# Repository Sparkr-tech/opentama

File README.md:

# OpenTama - An open-source reference design for MCUGotchi

## Synopsis

OpenTama is an open-source development board serving educational purposes, specifically designed for [MCUGotchi](https://github.com/jcrona/mcugotchi/) using [KiCad](https://www.kicad.org/).

It features:
* a low-power STM32L072CBT MCU
* either a backlit 128x64 LCD UC1701x or a 128x64 OLED SSD1306 display
* an RGB LED for notifications
* a piezoelectric speaker
* a 1000mAh battery
* a USB C connector for data and charging
* three buttons

Being an open-source hardware design, anyone can manufacture his/her own board. Furthermore, all components have been placed on the top side of the board, so that the assembly as well can be performed by EMS such as JLCPCB, even for small quantities. The battery and screen must be soldered manually.

## Build instructions
### Hardware

1. Make or buy an OpenTama board

	If you decide to build it, please note that the JLCPCB references for all the components have already been provided in the project. However, those have been selected depending on their availability at a specific point in time, and will probably need adjustments if you decide to go with JLCPCB.

2. Decide if you want an SSD1306 OLED screen or a UC1701x LCD screen, and buy it

	The UC1701x LCD is a low power display compared to the SSD1306 OLED that drains way more power. However, if you plan to use the MCUGotchi firmware, the highest power consumption will come from the MCU that will not really have time to sleep, so your choice will not have a big impact on the overall power consumption.

	If you want to use an SSD1306, the board expects a regular 7-pin 0,96" integrated module. However, if you want a UC1701x, you just need the LCD itself, and you can either choose an FPC one (0.5mm pitch, 14 pins), or one that needs to be soldered (0.6mm pitch, 14 pins).  
For reference, we used [this one](https://www.aliexpress.com/item/32828607106.html).

3. Buy a a battery

	The design has been made assuming a 1000mAh 40x30x12mm Li-Po/Li-ion battery.  
For reference, we used [this one](https://www.aliexpress.com/item/4000742443431.html).

4. Plug or solder the display

5. Solder the battery

6. Your OpenTama board is ready !

### Software
1. Build the firmware of your choosing

	For instance, checkout the [MCUGotchi](https://github.com/jcrona/mcugotchi/) repository and follow the instructions to build it for the OpenTama board.

2. Get and build [dfu-util](http://dfu-util.sourceforge.net/)

3. Boot the board in DFU mode

	Close the BOOT0 jumper at the top of the board, and while doing so, trigger a reset by connecting together the NRST and GND pins at the right of the board.

4. Program the board using __dfu-util__
```
$ cd mcugotchi
$ sudo make flash
```
or
```
$ sudo dfu-util -a 0 -s 0x08000000:leave -D <firmware.bin>
```

5. Enjoy !

## License

OpenTama is distributed under the CERN-OHL-S v2 license. See the LICENSE file for more information.

__  
Copyright (C) 2022 Sparkr

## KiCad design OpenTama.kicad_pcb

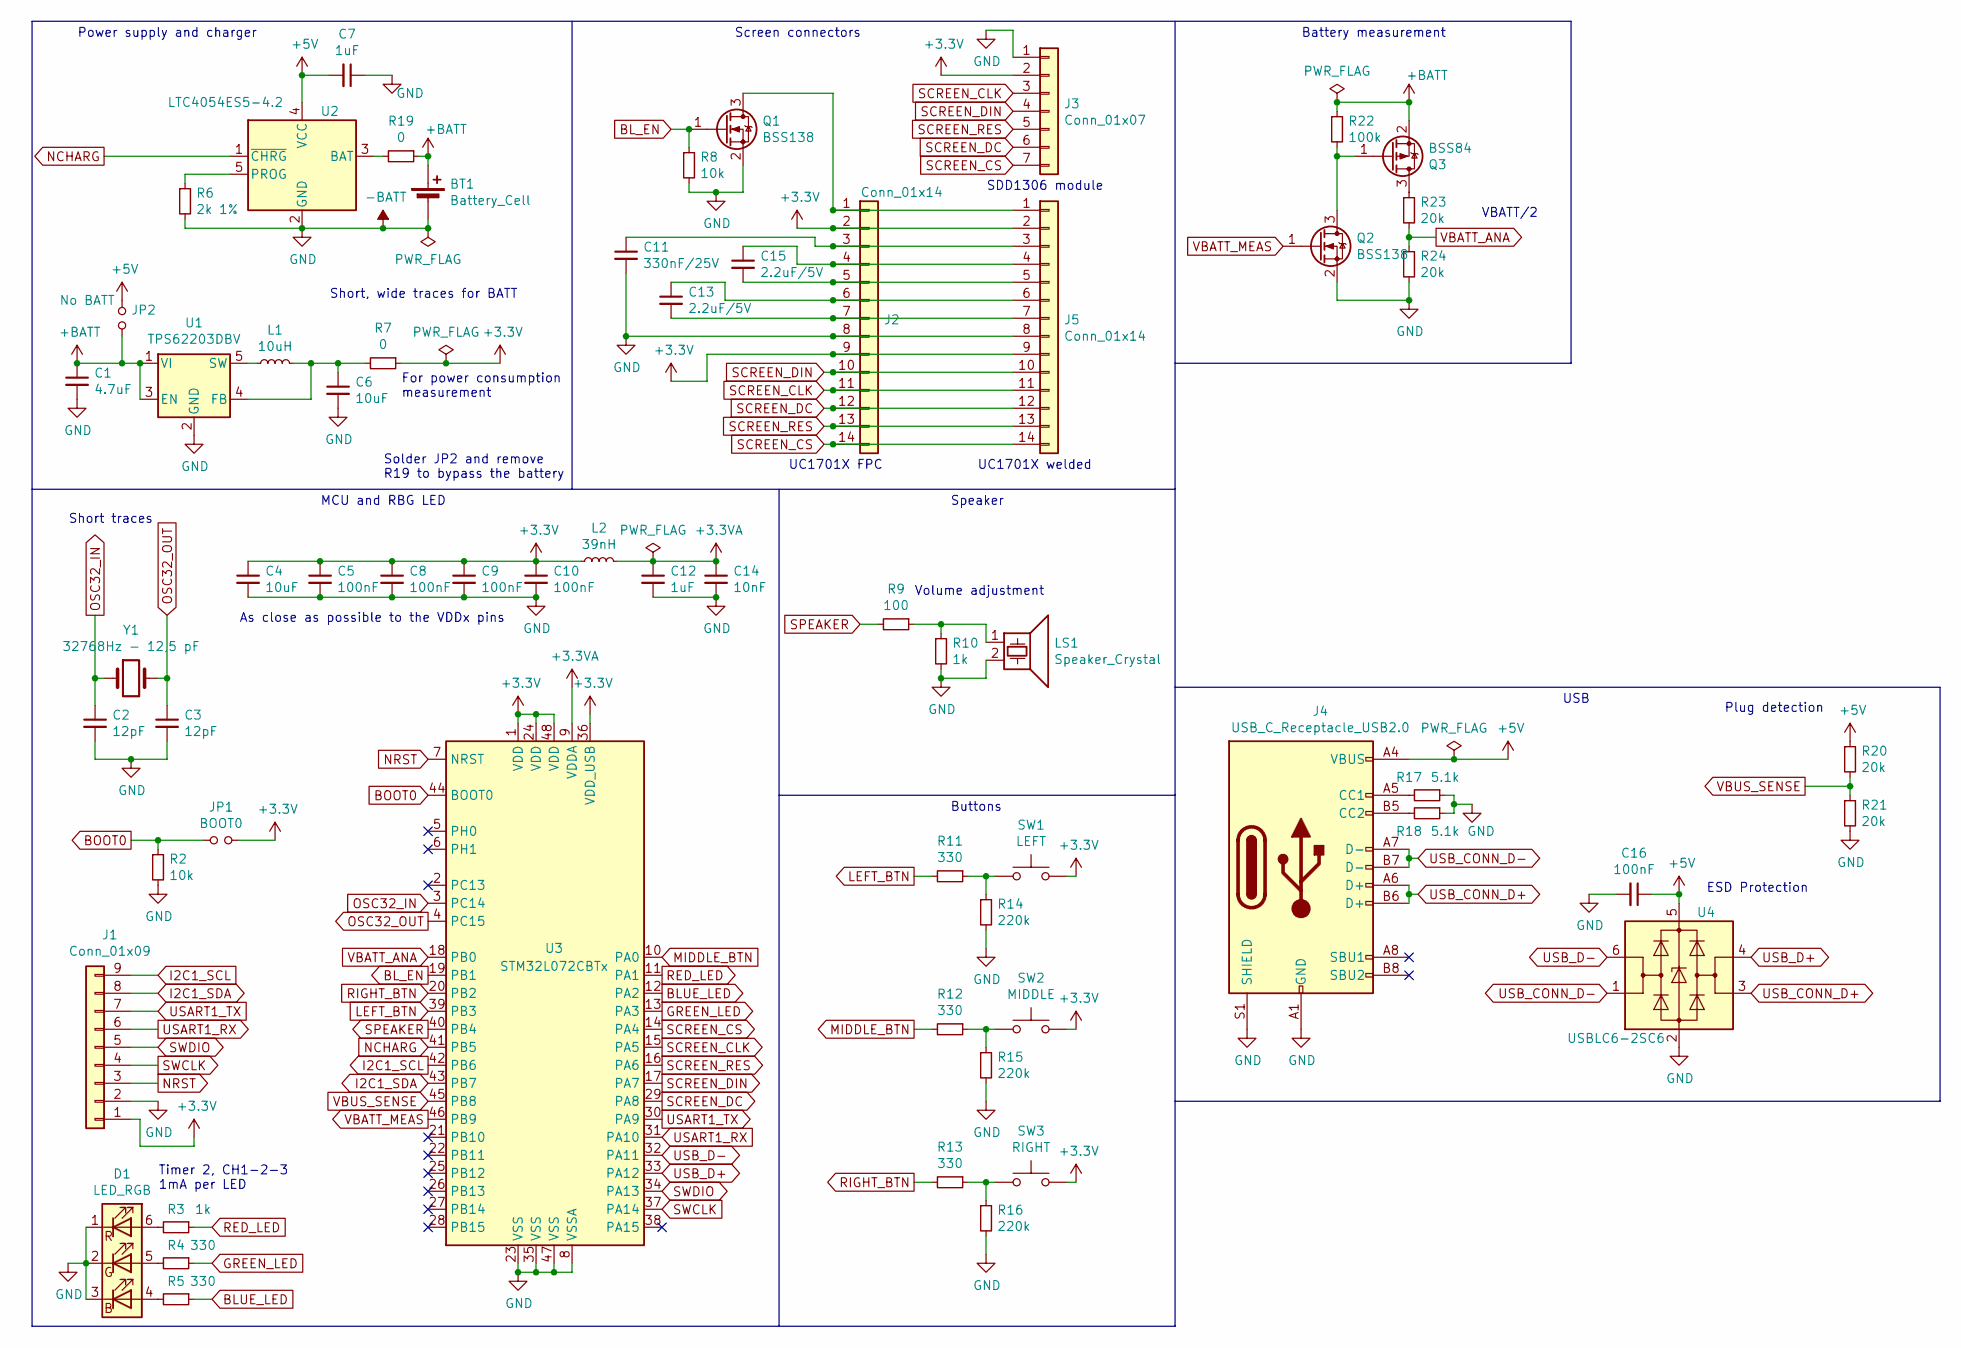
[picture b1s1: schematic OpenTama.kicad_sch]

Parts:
BT1: Battery_Cell; Battery_Pads_4x4
C1: 4.7uF; C_1206_3216Metric; LCSC C29823
C2, C3: 12pF; C_0402_1005Metric; LCSC C1547
C4: 10uF; C_0603_1608Metric; LCSC C19702
C5, C8, C9, C10: 100nF; C_0402_1005Metric; LCSC C1525
C6: 10uF; C_1206_3216Metric; LCSC C13585
C7: 1uF; C_1206_3216Metric; LCSC C1848
C11: 330nF/25V; C_0603_1608Metric; LCSC C1615
C12: 1uF; C_0603_1608Metric; LCSC C15849
C13, C15: 2.2uF/5V; C_0402_1005Metric; LCSC C12530
C14: 10nF; C_0402_1005Metric; LCSC C15195
C16: 100nF; C_0603_1608Metric; LCSC C14663
D1: LED_RGB; LED_RGB_TC5050; LCSC C784540
J1: Conn_01x09; PinHeader_1x09_P2.54mm_Vertical
J2: Conn_01x14; Hirose_FH34SRJ-14S-0.5SH_1x14-1MP_P0.50mm_Horizontal; LCSC C324724
J3: Conn_01x07; PinHeader_1x07_P2.54mm_Vertical
J4: USB_C_Receptacle_USB2.0; USB_C_Receptacle_HRO_TYPE-C-31-M-12; LCSC C165948
J5: Conn_01x14; LCD_14p_0.6mm
JP1: BOOT0; PinHeader_1x02_P2.54mm_Vertical
JP2: No BATT; SolderJumper-2_P1.3mm_Open_RoundedPad1.0x1.5mm
L1: 10uH; L_Sunlord_MWSA0518_5.4x5.2mm; LCSC C408412
L2: 39nH; L_0402_1005Metric; LCSC C26443
LS1: Speaker_Crystal; Buzzer_CUI_CPT-9019S-SMT; LCSC C391035
Q1, Q2: BSS138; SOT-23; LCSC C347484
Q3: BSS84; SOT-23; LCSC C8492
R2, R8: 10k; R_0402_1005Metric; LCSC C25744
R3: 1k; R_0603_1608Metric; LCSC C21190
R4, R5: 330; R_0603_1608Metric; LCSC C23138
R6: 2k 1%; R_0603_1608Metric; LCSC C22975
R7, R19: 0; R_0603_1608Metric; LCSC C21189
R9: 100; R_0402_1005Metric; LCSC C25076
R10: 1k; R_0402_1005Metric; LCSC C11702
R11, R12, R13: 330; R_0402_1005Metric; LCSC C25104
R14, R15, R16: 220k; R_0402_1005Metric; LCSC C25767
R17, R18: 5.1k; R_0402_1005Metric; LCSC C25905
R20, R21, R23, R24: 20k; R_0402_1005Metric; LCSC C25765
R22: 100k; R_0402_1005Metric; LCSC C25741
SW1: LEFT; SW_Push_1P1T_NO_6x6mm_H9.5mm; LCSC C221880
SW2: MIDDLE; SW_Push_1P1T_NO_6x6mm_H9.5mm; LCSC C221880
SW3: RIGHT; SW_Push_1P1T_NO_6x6mm_H9.5mm; LCSC C221880
U1: TPS62203DBV; SOT-23-5; LCSC C9051
U2: LTC4054ES5-4.2; TSOT-23-5; LCSC C462648
U3: STM32L072CBTx; LQFP-48_7x7mm_P0.5mm; LCSC C465977
U4: USBLC6-2SC6; SOT-23-6; LCSC C2827654
Y1: 32768Hz - 12,5 pF; Crystal_SMD_3215-2Pin_3.2x1.5mm; LCSC C32346

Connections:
+3.3VA: C12.1, C14.1, L2.2, U3.9 (VDDA)
+3V3: C4.1, C5.1, C8.1, C9.1, C10.1, J1.1, J2.2, J2.9, J3.2, J5.2, J5.9, JP1.2, L2.1, R7.1, SW1.2, SW2.2, SW3.2, U3.1 (VDD), U3.24 (VDD), U3.36 (VDD_USB), U3.48 (VDD)
+5V: C7.2, C16.1, J4.A4 (VBUS), J4.A9 (VBUS), J4.B4 (VBUS), J4.B9 (VBUS), JP2.1, R20.1, U2.4 (VCC), U4.5 (VBUS)
+BATT: BT1.1 (+), C1.1, JP2.2, Q3.2 (S), R19.1, R22.1, U1.1 (VI), U1.3 (EN)
-BATT: BT1.2 (-), C1.2, C2.2, C3.2, C4.2, C5.2, C6.2, C7.1, C8.2, C9.2, C10.2, C11.2, C12.2, C14.2, C16.2, D1.1 (RK), D1.2 (GK), D1.3 (BK), J1.2, J2.8, J3.1, J4.A1 (GND), J4.A12 (GND), J4.B1 (GND), J4.B12 (GND), J4.S1 (SHIELD), J5.8, LS1.2, Q1.2 (S), Q2.2 (S), R2.2, R6.2, R8.2, R10.2, R14.2, R15.2, R16.2, R17.1, R18.1, R21.2, R24.2, U1.2 (GND), U2.2 (GND), U3.8 (VSSA), U3.23 (VSS), U3.35 (VSS), U3.47 (VSS), U4.2 (GND)
BLUE_LED: R5.1, U3.12 (PA2)
BL_EN: Q1.1 (G), R8.1, U3.19 (PB1)
BOOT0: JP1.1, R2.1, U3.44 (BOOT0)
GREEN_LED: R4.1, U3.13 (PA3)
I2C1_SCL: J1.9, U3.42 (PB6)
I2C1_SDA: J1.8, U3.43 (PB7)
LEFT_BTN: R11.2, U3.39 (PB3)
MIDDLE_BTN: R12.2, U3.10 (PA0)
NCHARG: U2.1 (~CHRG), U3.41 (PB5)
NRST: J1.3, U3.7 (NRST)
unnamed: D1.4 (BA), R5.2
unnamed: D1.5 (GA), R4.2
unnamed: D1.6 (RA), R3.2
unnamed: J2.1, J5.1, Q1.3 (D)
unnamed: C11.1, J2.3, J5.3
unnamed: C15.1, J2.4, J5.4
unnamed: C15.2, J2.5, J5.5
unnamed: C13.1, J2.6, J5.6
unnamed: C13.2, J2.7, J5.7
unnamed: J4.A5 (CC1), R17.2
unnamed: J4.B5 (CC2), R18.2
unnamed: LS1.1, R9.1, R10.1
unnamed: Q2.3 (D), Q3.1 (G), R22.2
unnamed: Q3.3 (D), R23.1
unnamed: R11.1, R14.1, SW1.1
unnamed: R12.1, R15.1, SW2.1
unnamed: R13.1, R16.1, SW3.1
unnamed: C6.1, L1.2, R7.2, U1.4 (FB)
unnamed: L1.1, U1.5 (SW)
unnamed: R19.2, U2.3 (BAT)
unnamed: R6.1, U2.5 (PROG)
OSC32_IN: C2.1, U3.3 (PC14), Y1.1
OSC32_OUT: C3.1, U3.4 (PC15), Y1.2
RED_LED: R3.1, U3.11 (PA1)
RIGHT_BTN: R13.2, U3.20 (PB2)
SCREEN_CLK: J2.11, J3.3, J5.11, U3.15 (PA5)
SCREEN_CS: J2.14, J3.7, J5.14, U3.14 (PA4)
SCREEN_DC: J2.12, J3.6, J5.12, U3.29 (PA8)
SCREEN_DIN: J2.10, J3.4, J5.10, U3.17 (PA7)
SCREEN_RES: J2.13, J3.5, J5.13, U3.16 (PA6)
SPEAKER: R9.2, U3.40 (PB4)
SWCLK: J1.4, U3.37 (PA14)
SWDIO: J1.5, U3.34 (PA13)
USART1_RX: J1.6, U3.31 (PA10)
USART1_TX: J1.7, U3.30 (PA9)
USB_CONN_D+: J4.A6 (D+), J4.B6 (D+), U4.3 (I/O2)
USB_CONN_D-: J4.A7 (D-), J4.B7 (D-), U4.1 (I/O1)
USB_D+: U3.33 (PA12), U4.4 (I/O2)
USB_D-: U3.32 (PA11), U4.6 (I/O1)
VBATT_ANA: R23.2, R24.1, U3.18 (PB0)
VBATT_MEAS: Q2.1 (G), U3.46 (PB9)
VBUS_SENSE: R20.2, R21.1, U3.45 (PB8)

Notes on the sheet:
Power supply and charger
Solder JP2 and remove R19 to bypass the battery
Short traces
ESD Protection
Short, wide traces for BATT
Battery measurement
VBATT/2
Speaker
USB
Timer 2, CH1-2-3 1mA per LED
As close as possible to the VDDx pins
Plug detection
SDD1306 module
MCU and RBG LED
For power consumption measurement
UC1701X FPC
UC1701X welded
Volume adjustment
Screen connectors
Buttons

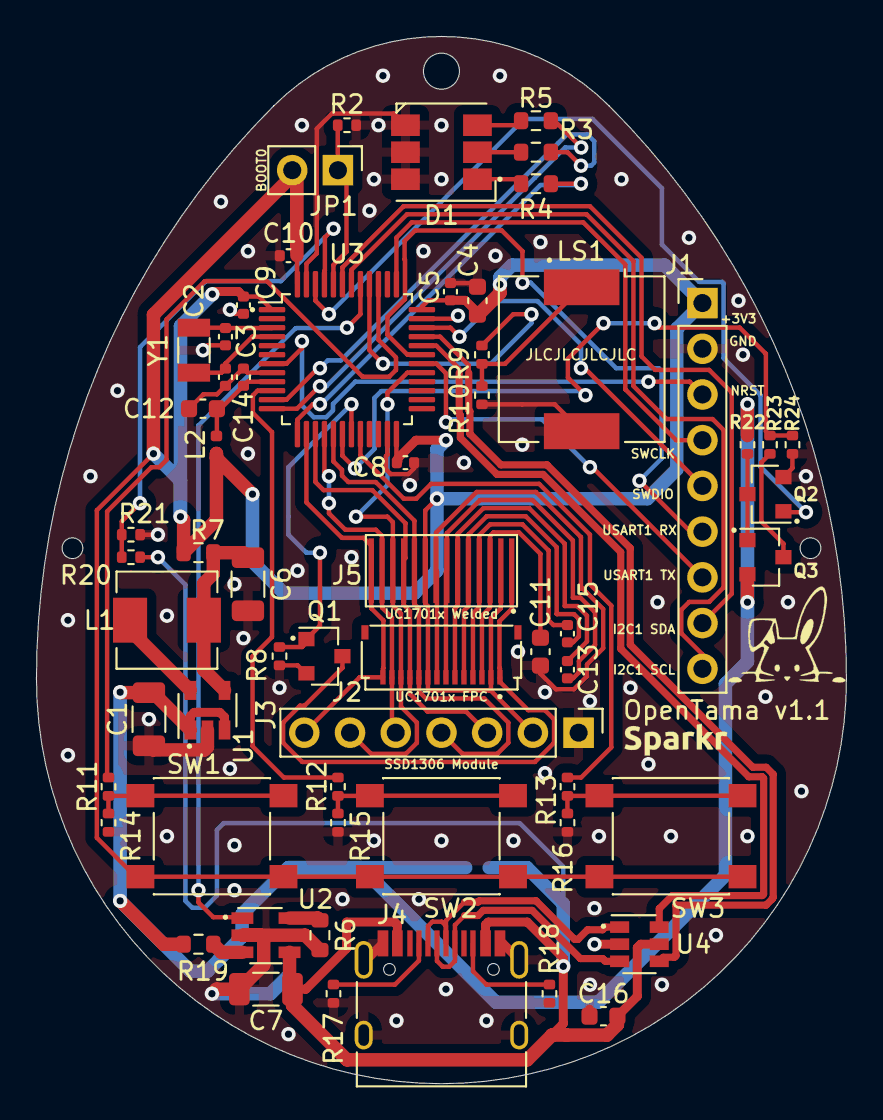
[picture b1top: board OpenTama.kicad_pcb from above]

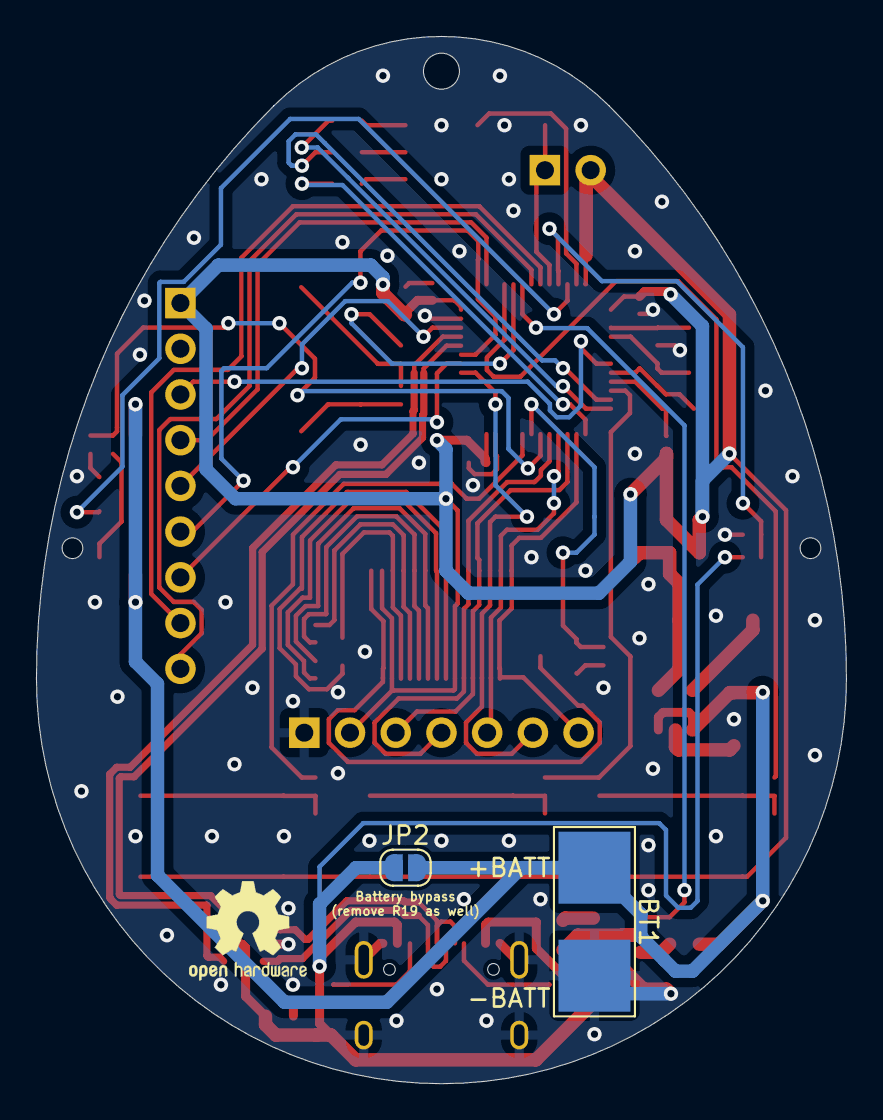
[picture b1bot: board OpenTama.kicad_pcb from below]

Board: 2 copper layers, 45.0 x 58.2 mm, 62 parts (2 on the bottom side), 57 nets.

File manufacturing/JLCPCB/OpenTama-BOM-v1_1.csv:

Comment,Designator,Footprint,JLCPCB Part #
"Battery_Cell","BT1","OpenTama:Battery_Pads_4x4",""
"4.7uF","C1","Capacitor_SMD:C_1206_3216Metric","C29823"
"330nF/25V","C11","Capacitor_SMD:C_0603_1608Metric","C1615"
"1uF","C12","Capacitor_SMD:C_0603_1608Metric","C15849"
"2.2uF/5V","C13,C15","Capacitor_SMD:C_0402_1005Metric","C12530"
"10nF","C14","Capacitor_SMD:C_0402_1005Metric","C15195"
"100nF","C16","Capacitor_SMD:C_0603_1608Metric","C14663"
"12pF","C2,C3","Capacitor_SMD:C_0402_1005Metric","C1547"
"10uF","C4","Capacitor_SMD:C_0603_1608Metric","C19702"
"100nF","C5,C8,C9,C10","Capacitor_SMD:C_0402_1005Metric","C1525"
"10uF","C6","Capacitor_SMD:C_1206_3216Metric","C13585"
"1uF","C7","Capacitor_SMD:C_1206_3216Metric","C1848"
"LED_RGB","D1","OpenTama:LED_RGB_TC5050","C784540"
"Conn_01x09","J1","Connector_PinHeader_2.54mm:PinHeader_1x09_P2.54mm_Vertical",""
"Conn_01x14","J2","OpenTama:Hirose_FH34SRJ-14S-0.5SH_1x14-1MP_P0.50mm_Horizontal","C324724"
"Conn_01x07","J3","Connector_PinHeader_2.54mm:PinHeader_1x07_P2.54mm_Vertical",""
"USB_C_Receptacle_USB2.0","J4","Connector_USB:USB_C_Receptacle_HRO_TYPE-C-31-M-12","C165948"
"BOOT0","JP1","Connector_PinHeader_2.54mm:PinHeader_1x02_P2.54mm_Vertical",""
"No BATT","JP2","Jumper:SolderJumper-2_P1.3mm_Open_RoundedPad1.0x1.5mm",""
"10uH","L1","Inductor_SMD:L_Sunlord_MWSA0518_5.4x5.2mm","C408412"
"39nH","L2","Inductor_SMD:L_0402_1005Metric","C26443"
"Speaker_Crystal","LS1","Buzzer_Beeper:Buzzer_CUI_CPT-9019S-SMT","C391035"
"BSS138","Q1,Q2","Package_TO_SOT_SMD:SOT-23","C347484"
"BSS84","Q3","Package_TO_SOT_SMD:SOT-23","C8492"
"1k","R10","Resistor_SMD:R_0402_1005Metric","C11702"
"330","R11,R12,R13","Resistor_SMD:R_0402_1005Metric","C25104"
"220k","R14,R15,R16","Resistor_SMD:R_0402_1005Metric","C25767"
"5.1k","R17,R18","Resistor_SMD:R_0402_1005Metric","C25905"
"10k","R2,R8","Resistor_SMD:R_0402_1005Metric","C25744"
"100k","R22","Resistor_SMD:R_0402_1005Metric","C25741"
"20k","R20,R21,R23,R24","Resistor_SMD:R_0402_1005Metric","C25765"
"1k","R3","Resistor_SMD:R_0603_1608Metric","C21190"
"330","R4,R5","Resistor_SMD:R_0603_1608Metric","C23138"
"2k 1%","R6","Resistor_SMD:R_0603_1608Metric","C22975"
"0","R7,R19","Resistor_SMD:R_0603_1608Metric","C21189"
"100","R9","Resistor_SMD:R_0402_1005Metric","C25076"
"LEFT","SW1","Button_Switch_SMD:SW_Push_1P1T_NO_6x6mm_H9.5mm","C221880"
"MIDDLE","SW2","Button_Switch_SMD:SW_Push_1P1T_NO_6x6mm_H9.5mm","C221880"
"RIGHT","SW3","Button_Switch_SMD:SW_Push_1P1T_NO_6x6mm_H9.5mm","C221880"
"TPS62203DBV","U1","Package_TO_SOT_SMD:SOT-23-5","C9051"
"LTC4054ES5-4.2","U2","Package_TO_SOT_SMD:TSOT-23-5","C462648"
"STM32L072CBTx","U3","Package_QFP:LQFP-48_7x7mm_P0.5mm","C465977"
"USBLC6-2SC6","U4","Package_TO_SOT_SMD:SOT-23-6","C2827654"
"32768Hz - 12,5 pF","Y1","Crystal:Crystal_SMD_3215-2Pin_3.2x1.5mm","C32346"

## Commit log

2022-04-19 Initial release of the OpenTama board
2023-04-19 Use LCSC instead of JLCPCB in symbol props
2023-05-02 Upgrade project to KiCad 7
2023-06-15 Remove exported BOM
2023-06-15 Ignore only .csv at top level
2023-06-15 Add v1.1 manufacturing files for JLCPCB
    Those files have been fixed manually to match JLCPCB's online tool.
2023-07-12 Add missing -cache.lib file
2023-07-12 Migration to KiCAD 7.0
2023-07-12 Fix project (ERC)
2023-07-12 Ignore -backups folder
2023-07-12 Add JLCRotOffset (thx kabili207)

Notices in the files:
OpenTama.kicad_pcb:
Licensed under CERN-OHL-S v2
